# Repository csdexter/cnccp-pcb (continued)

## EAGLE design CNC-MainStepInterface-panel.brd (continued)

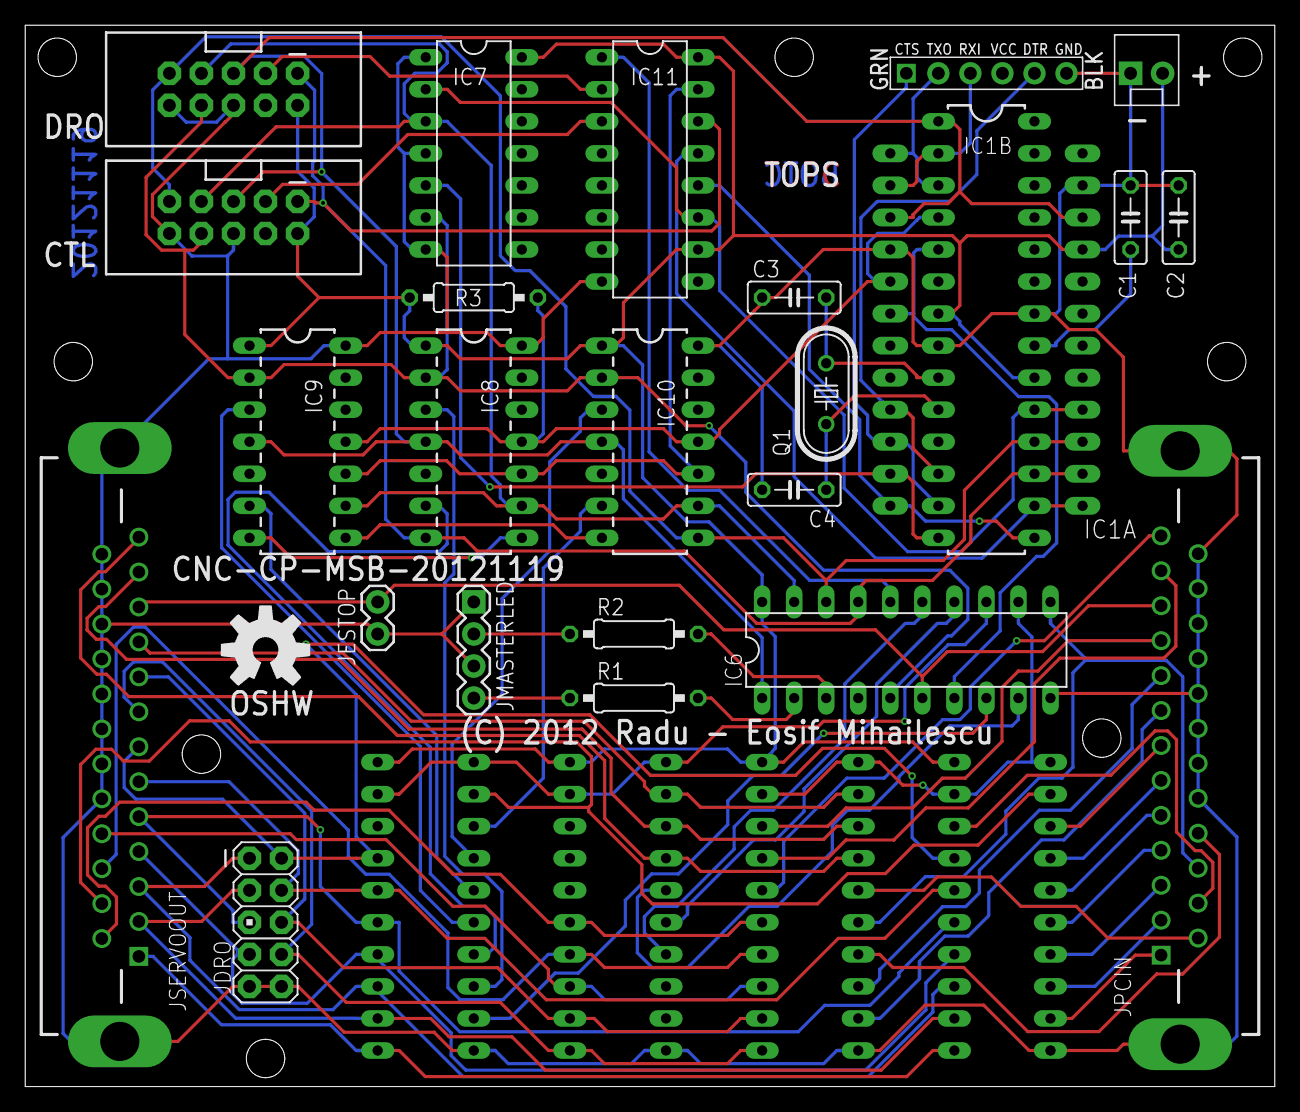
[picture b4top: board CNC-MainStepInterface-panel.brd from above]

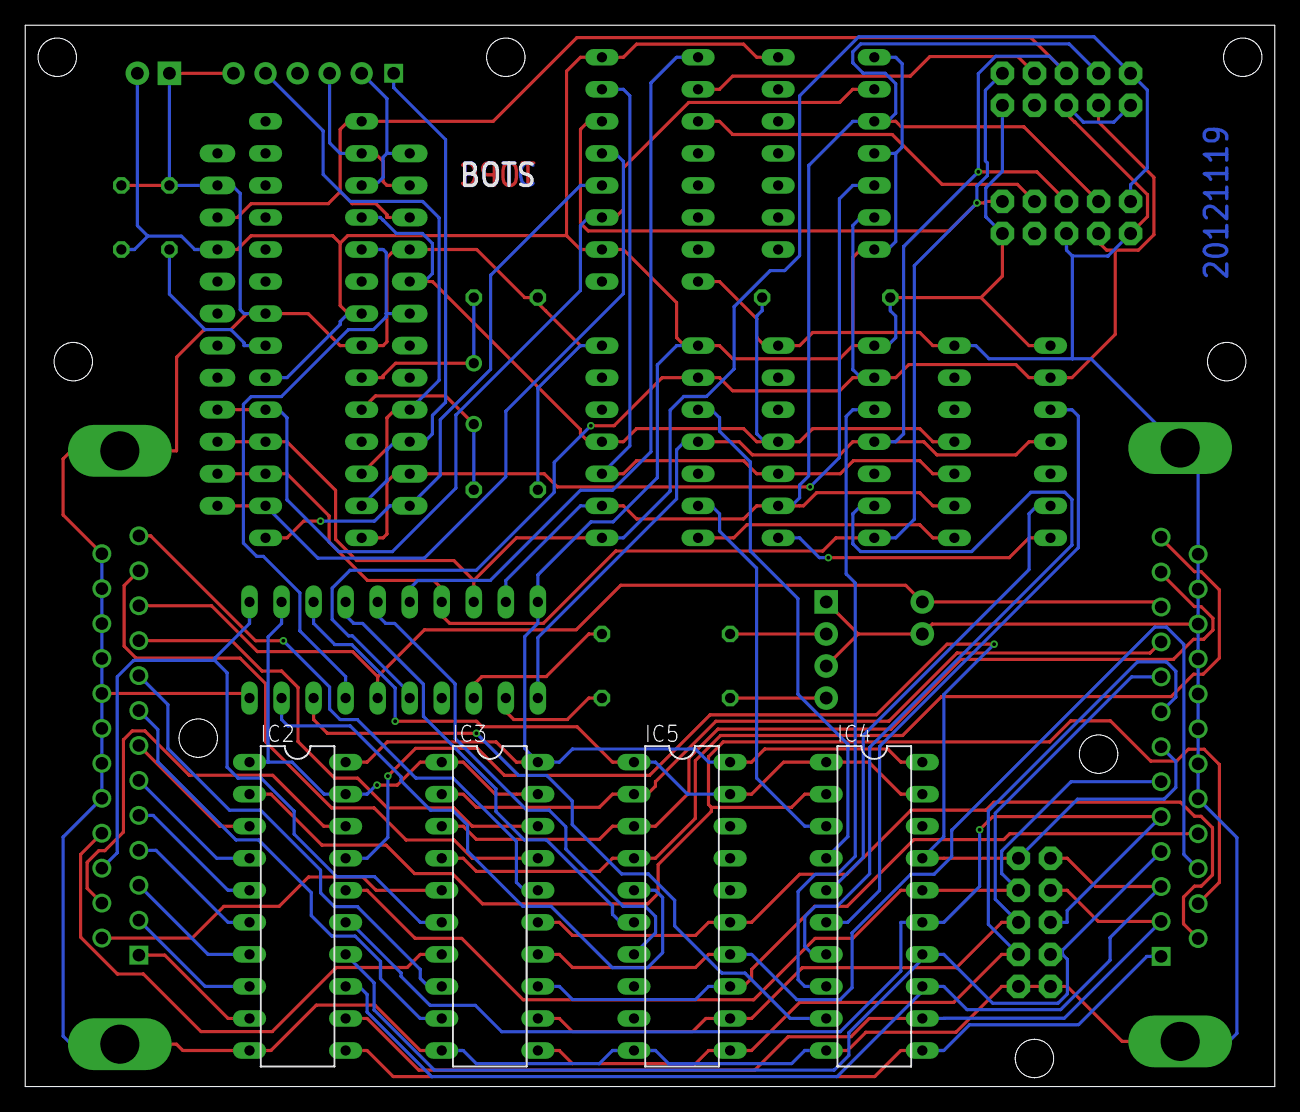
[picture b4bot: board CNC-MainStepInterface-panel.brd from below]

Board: 2 copper layers, 99.1 x 84.1 mm, 30 parts (4 on the bottom side), 78 nets.

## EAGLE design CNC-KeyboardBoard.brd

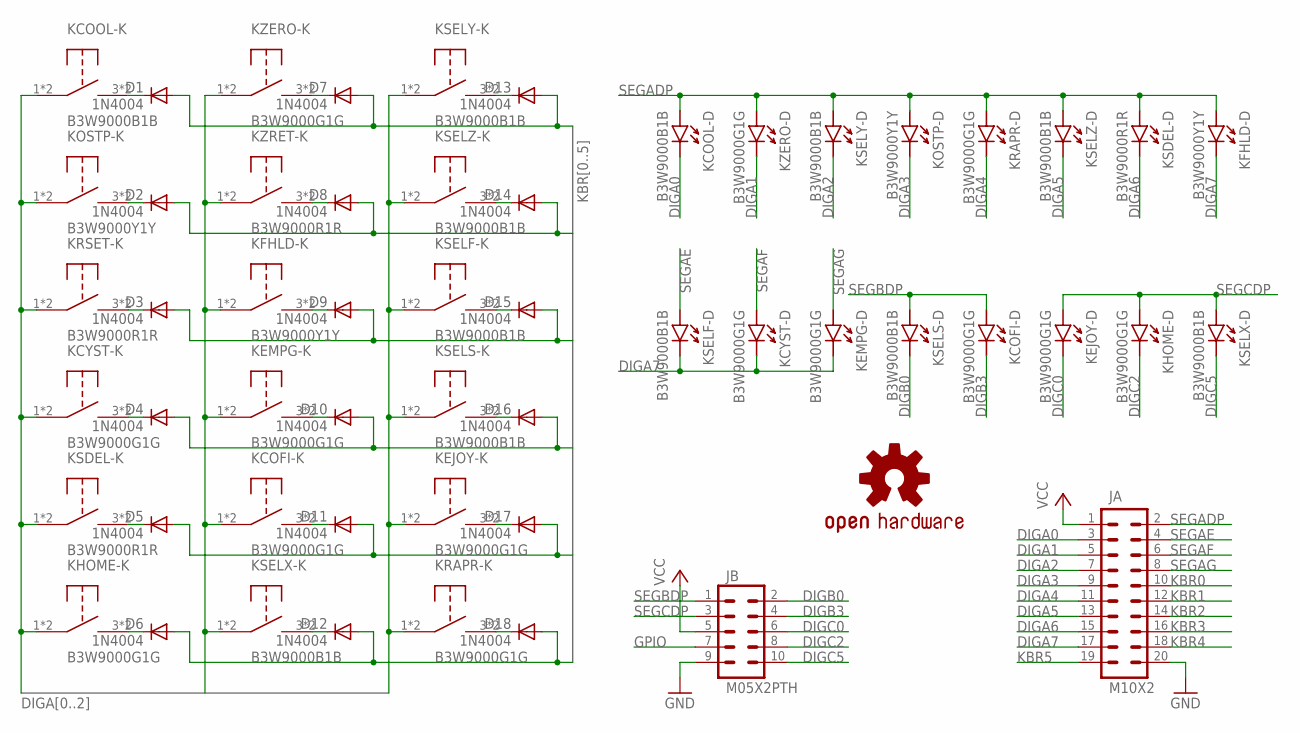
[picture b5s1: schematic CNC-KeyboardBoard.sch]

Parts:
D1, D2, D3, D4, D5, D6, D7, D8, D9, D10, D11, D12, D13, D14, D15, D16, D17, D18: 1N4004; DO41-10
JA: M10X2; 2X10
JB: M05X2PTH; AVR_ICSP
KCOFI: B3W9000G1G; OMRON_B3W90
KCOOL: B3W9000B1B; OMRON_B3W90
KCYST: B3W9000G1G; OMRON_B3W90
KEJOY: B3W9000G1G; OMRON_B3W90
KEMPG: B3W9000G1G; OMRON_B3W90
KFHLD: B3W9000Y1Y; OMRON_B3W90
KHOME: B3W9000G1G; OMRON_B3W90
KOSTP: B3W9000Y1Y; OMRON_B3W90
KRAPR: B3W9000G1G; OMRON_B3W90
KRSET: B3W9000R1R; OMRON_B3W90
KSDEL: B3W9000R1R; OMRON_B3W90
KSELF: B3W9000B1B; OMRON_B3W90
KSELS: B3W9000B1B; OMRON_B3W90
KSELX: B3W9000B1B; OMRON_B3W90
KSELY: B3W9000B1B; OMRON_B3W90
KSELZ: B3W9000B1B; OMRON_B3W90
KZERO: B3W9000G1G; OMRON_B3W90
KZRET: B3W9000R1R; OMRON_B3W90
U$1: SPARKFUN_OSHW-LOGOL; SPARKFUN_OSHW-LOGO-L

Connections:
DIGA0: JA.3, KCOOL.1, KCOOL.2, KCOOL.6 (K), KCYST.1, KCYST.2, KHOME.1, KHOME.2, KOSTP.1, KOSTP.2, KRSET.1, KRSET.2, KSDEL.1, KSDEL.2
DIGA1: JA.5, KCOFI.1, KCOFI.2, KEMPG.1, KEMPG.2, KFHLD.1, KFHLD.2, KSELX.1, KSELX.2, KZERO.1, KZERO.2, KZERO.6 (K), KZRET.1, KZRET.2
DIGA2: JA.7, KEJOY.1, KEJOY.2, KRAPR.1, KRAPR.2, KSELF.1, KSELF.2, KSELS.1, KSELS.2, KSELY.1, KSELY.2, KSELY.6 (K), KSELZ.1, KSELZ.2
DIGA3: JA.9, KOSTP.6 (K)
DIGA4: JA.11, KRAPR.6 (K)
DIGA5: JA.13, KSELZ.6 (K)
DIGA6: JA.15, KSDEL.6 (K)
DIGA7: JA.17, KCYST.6 (K), KEMPG.6 (K), KFHLD.6 (K), KSELF.6 (K)
DIGB0: JB.2, KSELS.6 (K)
DIGB3: JB.4, KCOFI.6 (K)
DIGC0: JB.6, KEJOY.6 (K)
DIGC2: JB.8, KHOME.6 (K)
DIGC5: JB.10, KSELX.6 (K)
GND: JA.20, JB.9
GPIO: JB.7
KBR0: D1.A, D7.A, D13.A, JA.10
KBR1: D2.A, D8.A, D14.A, JA.12
KBR2: D3.A, D9.A, D15.A, JA.14
KBR3: D4.A, D10.A, D16.A, JA.16
KBR4: D5.A, D11.A, D17.A, JA.18
KBR5: D6.A, D12.A, D18.A, JA.19
unnamed: D3.C, KRSET.3, KRSET.4
unnamed: D4.C, KCYST.3, KCYST.4
unnamed: D5.C, KSDEL.3, KSDEL.4
unnamed: D6.C, KHOME.3, KHOME.4
unnamed: D1.C, KCOOL.3, KCOOL.4
unnamed: D7.C, KZERO.3, KZERO.4
unnamed: D8.C, KZRET.3, KZRET.4
unnamed: D9.C, KFHLD.3, KFHLD.4
unnamed: D11.C, KCOFI.3, KCOFI.4
unnamed: D12.C, KSELX.3, KSELX.4
unnamed: D10.C, KEMPG.3, KEMPG.4
unnamed: D2.C, KOSTP.3, KOSTP.4
unnamed: D16.C, KSELS.3, KSELS.4
unnamed: D13.C, KSELY.3, KSELY.4
unnamed: D14.C, KSELZ.3, KSELZ.4
unnamed: D15.C, KSELF.3, KSELF.4
unnamed: D17.C, KEJOY.3, KEJOY.4
unnamed: D18.C, KRAPR.3, KRAPR.4
SEGADP: JA.2, KCOOL.5 (A), KFHLD.5 (A), KOSTP.5 (A), KRAPR.5 (A), KSDEL.5 (A), KSELY.5 (A), KSELZ.5 (A), KZERO.5 (A)
SEGAE: JA.4, KSELF.5 (A)
SEGAF: JA.6, KCYST.5 (A)
SEGAG: JA.8, KEMPG.5 (A)
SEGBDP: JB.1, KCOFI.5 (A), KSELS.5 (A)
SEGCDP: JB.3, KEJOY.5 (A), KHOME.5 (A), KSELX.5 (A)
VCC: JA.1, JB.5

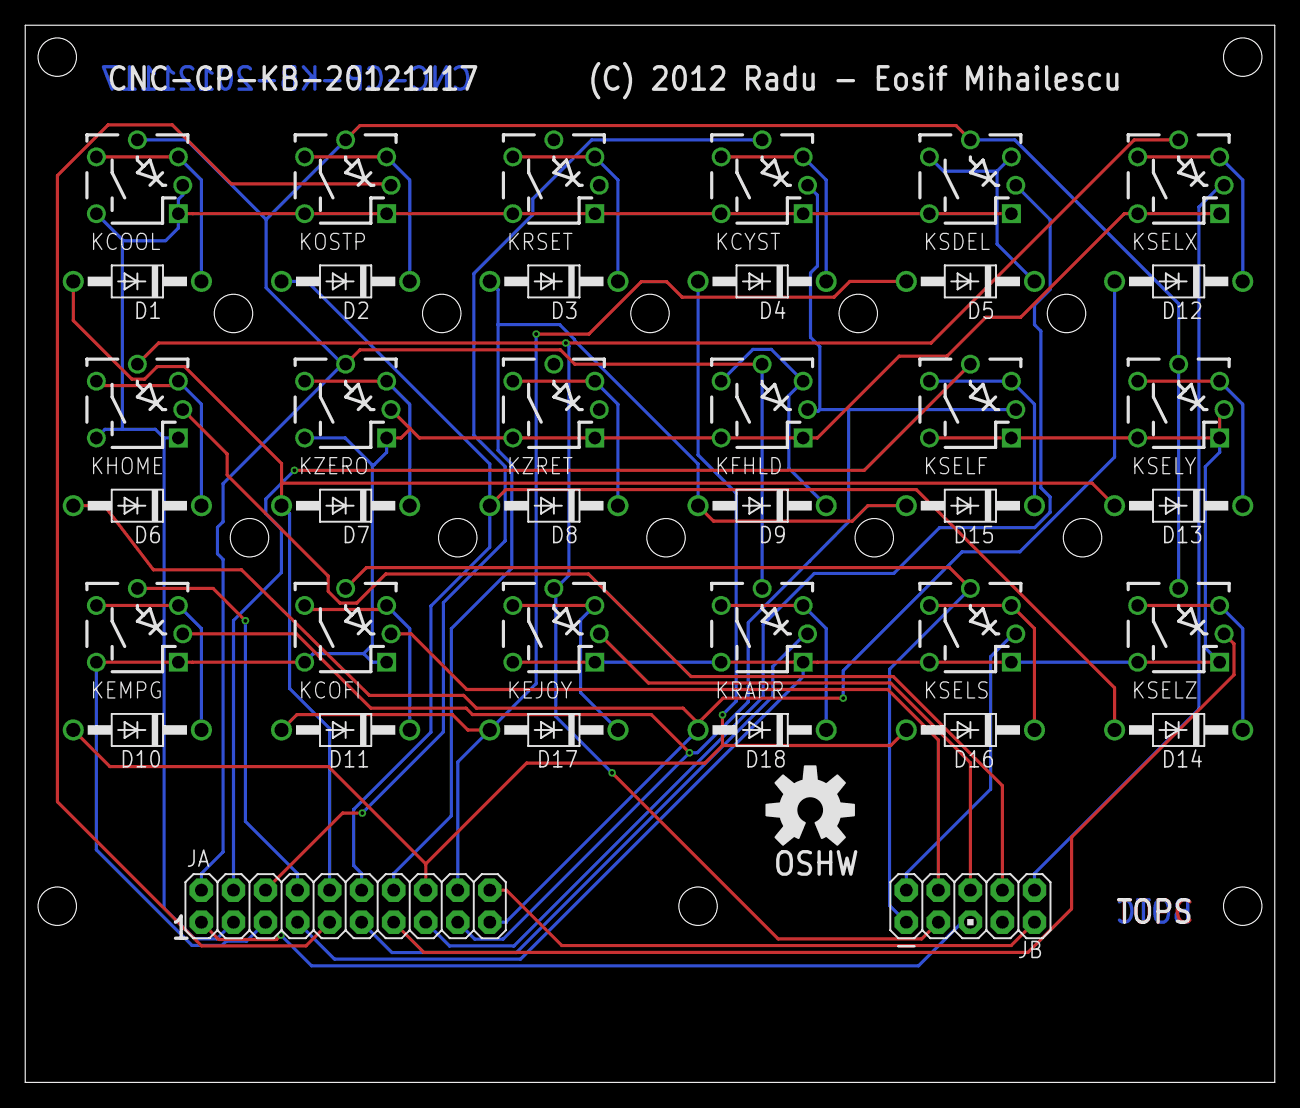
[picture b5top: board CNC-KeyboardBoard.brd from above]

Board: 2 copper layers, 99.1 x 83.8 mm, 39 parts (0 on the bottom side), 45 nets.

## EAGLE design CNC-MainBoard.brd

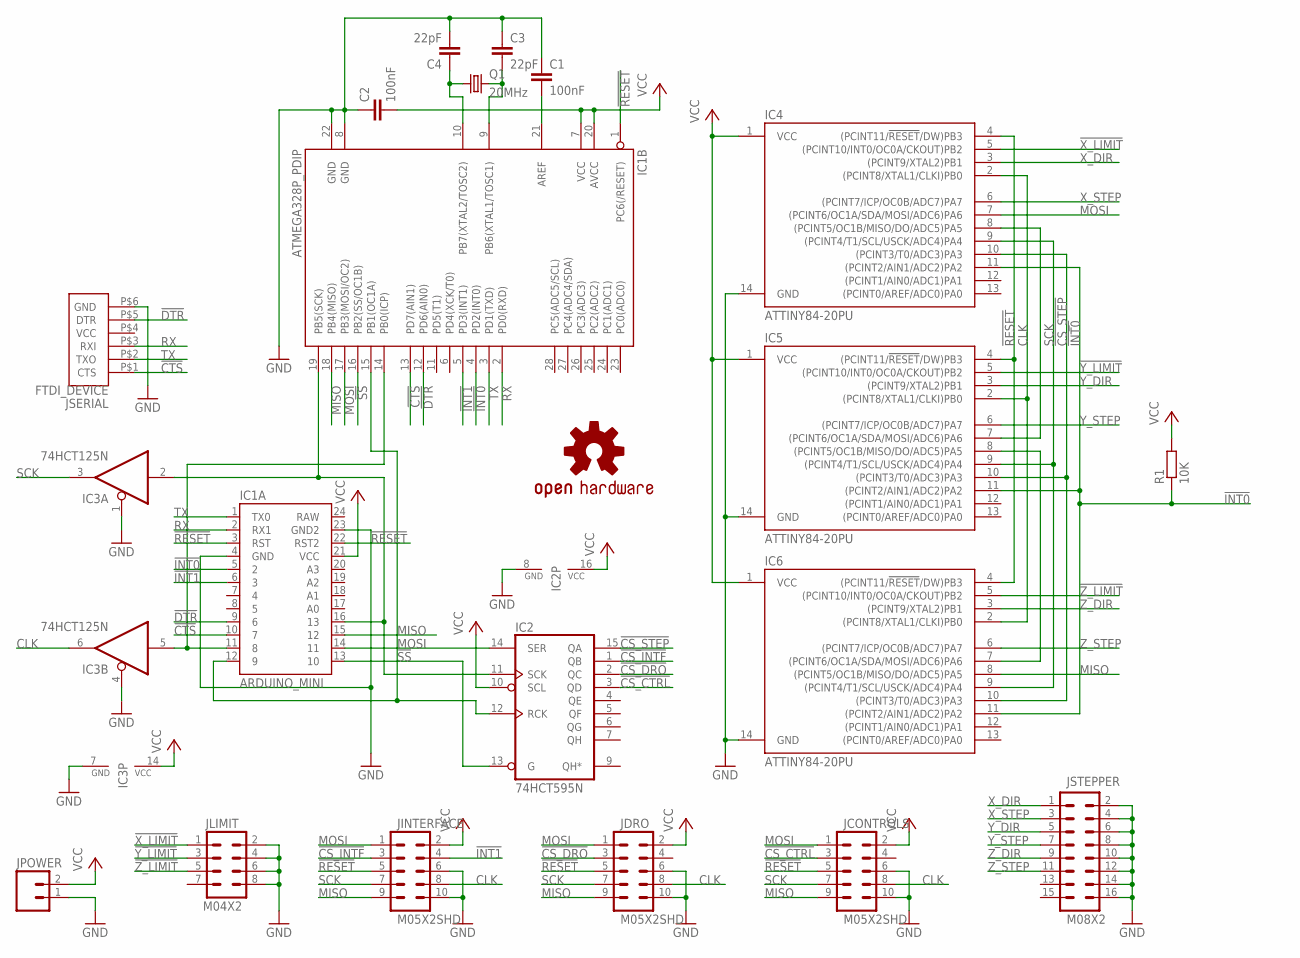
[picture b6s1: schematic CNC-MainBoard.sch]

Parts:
C1, C2: 100nF; C050-025X075
C3, C4: 22pF; C050-025X075
IC1A: ARDUINO_MINI
IC1B: ATMEGA328P_PDIP; DIL28-3
IC2: 74HCT595N; DIL16
IC3: 74HCT125N; DIL14
IC4, IC5, IC6: ATTINY84-20PU; DIL14
JCONTROLS: M05X2SHD; 2X5-SHROUDED
JDRO: M05X2SHD; 2X5-SHROUDED
JINTERFACE: M05X2SHD; 2X5-SHROUDED
JLIMIT: M04X2; 2X4
JPOWER: M02POLAR; MOLEX-1X2
JSERIAL: FTDI_DEVICE; FTDI_DEVICE_SIDE
JSTEPPER: M08X2; 2X8
Q1: 20MHz; HC49U-V
R1: 10K; 0207/10
U$1: SPARKFUN_OSHW-LOGOL; SPARKFUN_OSHW-LOGO-L

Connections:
!CS_CTRL: IC2.3 (QD), JCONTROLS.3
!CS_DRO: IC2.2 (QC), JDRO.3
!CS_INTF: IC2.1 (QB), JINTERFACE.3
!CS_STEP: IC2.15 (QA), IC4.10 ((PCINT3/T0/ADC3)PA3), IC5.10 ((PCINT3/T0/ADC3)PA3), IC6.10 ((PCINT3/T0/ADC3)PA3)
!CTS: IC1A.10 (7), IC1B.13 (PD7(AIN1)), JSERIAL.P$1 (CTS)
!DTR: IC1A.9 (6), IC1B.12 (PD6(AIN0)), JSERIAL.P$5 (DTR)
!INT0: IC1A.5 (2), IC1B.4 (PD2(INT0)), IC4.11 ((PCINT2/AIN1/ADC2)PA2), IC5.11 ((PCINT2/AIN1/ADC2)PA2), IC6.11 ((PCINT2/AIN1/ADC2)PA2), R1.1
!INT1: IC1A.6 (3), IC1B.5 (PD3(INT1)), JINTERFACE.4
!RESET: IC1A.3 (RST), IC1A.22 (RST2), IC1B.1 (PC6(/RESET)), IC4.4 ((PCINT11/!RESET!/DW)PB3), IC5.4 ((PCINT11/!RESET!/DW)PB3), IC6.4 ((PCINT11/!RESET!/DW)PB3), JCONTROLS.5, JDRO.5, JINTERFACE.5
!SS: IC1A.13 (10), IC1B.16 (PB2(SS/OC1B)), IC2.13 (G)
!X_LIMIT: IC4.5 ((PCINT10/INT0/OC0A/CKOUT)PB2), JLIMIT.1
!Y_LIMIT: IC5.5 ((PCINT10/INT0/OC0A/CKOUT)PB2), JLIMIT.3
!Z_LIMIT: IC6.5 ((PCINT10/INT0/OC0A/CKOUT)PB2), JLIMIT.5
CLK: IC3.6 (O), IC4.2 ((PCINT8/XTAL1/CLKI)PB0), IC5.2 ((PCINT8/XTAL1/CLKI)PB0), IC6.2 ((PCINT8/XTAL1/CLKI)PB0), JCONTROLS.8, JDRO.8, JINTERFACE.8
CLK_INT: IC1A.11 (8), IC1B.14 (PB0(ICP)), IC3.5 (I)
GND: C1.1, C2.1, C3.1, C4.2, IC1A.4 (GND), IC1A.23 (GND2), IC1B.8 (GND), IC1B.22 (GND), IC2.8 (GND), IC3.1 (OE), IC3.4 (OE), IC3.7 (GND), IC4.14 (GND), IC5.14 (GND), IC6.14 (GND), JCONTROLS.6, JCONTROLS.10, JDRO.6, JDRO.10, JINTERFACE.6, JINTERFACE.10, JLIMIT.2, JLIMIT.4, JLIMIT.6, JLIMIT.8, JPOWER.1, JSERIAL.P$6 (GND), JSTEPPER.2, JSTEPPER.4, JSTEPPER.6, JSTEPPER.8, JSTEPPER.10, JSTEPPER.12, JSTEPPER.14, JSTEPPER.16
MISO: IC1A.15 (12), IC1B.18 (PB4(MISO)), IC6.8 ((PCINT5/OC1B/MISO/DO/ADC5)PA5), JCONTROLS.9, JDRO.9, JINTERFACE.9
MISO_1: IC4.8 ((PCINT5/OC1B/MISO/DO/ADC5)PA5), IC5.7 ((PCINT6/OC1A/SDA/MOSI/ADC6)PA6)
MISO_2: IC5.8 ((PCINT5/OC1B/MISO/DO/ADC5)PA5), IC6.7 ((PCINT6/OC1A/SDA/MOSI/ADC6)PA6)
MOSI: IC1A.14 (11), IC1B.17 (PB3(MOSI/OC2)), IC2.14 (SER), IC4.7 ((PCINT6/OC1A/SDA/MOSI/ADC6)PA6), JCONTROLS.1, JDRO.1, JINTERFACE.1
unnamed: C1.2, IC1B.21 (AREF)
unnamed: C3.2, IC1B.9 (PB6(XTAL1/TOSC1)), Q1.2
unnamed: C4.1, IC1B.10 (PB7(XTAL2/TOSC2)), Q1.1
RX: IC1A.2 (RX1), IC1B.2 (PD0(RXD)), JSERIAL.P$3 (RXI)
SADDR: IC1A.12 (9), IC1B.15 (PB1(OC1A)), IC2.12 (RCK)
SCK: IC3.3 (O), IC4.9 ((PCINT4/T1/SCL/USCK/ADC4)PA4), IC5.9 ((PCINT4/T1/SCL/USCK/ADC4)PA4), IC6.9 ((PCINT4/T1/SCL/USCK/ADC4)PA4), JCONTROLS.7, JDRO.7, JINTERFACE.7
SCK_INT: IC1A.16 (13), IC1B.19 (PB5(SCK)), IC2.11 (SCK), IC3.2 (I)
TX: IC1A.1 (TX0), IC1B.3 (PD1(TXD)), JSERIAL.P$2 (TXO)
VCC: C2.2, IC1A.21 (VCC), IC1B.7 (VCC), IC1B.20 (AVCC), IC2.10 (SCL), IC2.16 (VCC), IC3.14 (VCC), IC4.1 (VCC), IC5.1 (VCC), IC6.1 (VCC), JCONTROLS.2, JDRO.2, JINTERFACE.2, JPOWER.2, R1.2
X_DIR: IC4.3 ((PCINT9/XTAL2)PB1), JSTEPPER.1
X_STEP: IC4.6 ((PCINT7/ICP/OC0B/ADC7)PA7), JSTEPPER.3
Y_DIR: IC5.3 ((PCINT9/XTAL2)PB1), JSTEPPER.5
Y_STEP: IC5.6 ((PCINT7/ICP/OC0B/ADC7)PA7), JSTEPPER.7
Z_DIR: IC6.3 ((PCINT9/XTAL2)PB1), JSTEPPER.9
Z_STEP: IC6.6 ((PCINT7/ICP/OC0B/ADC7)PA7), JSTEPPER.11

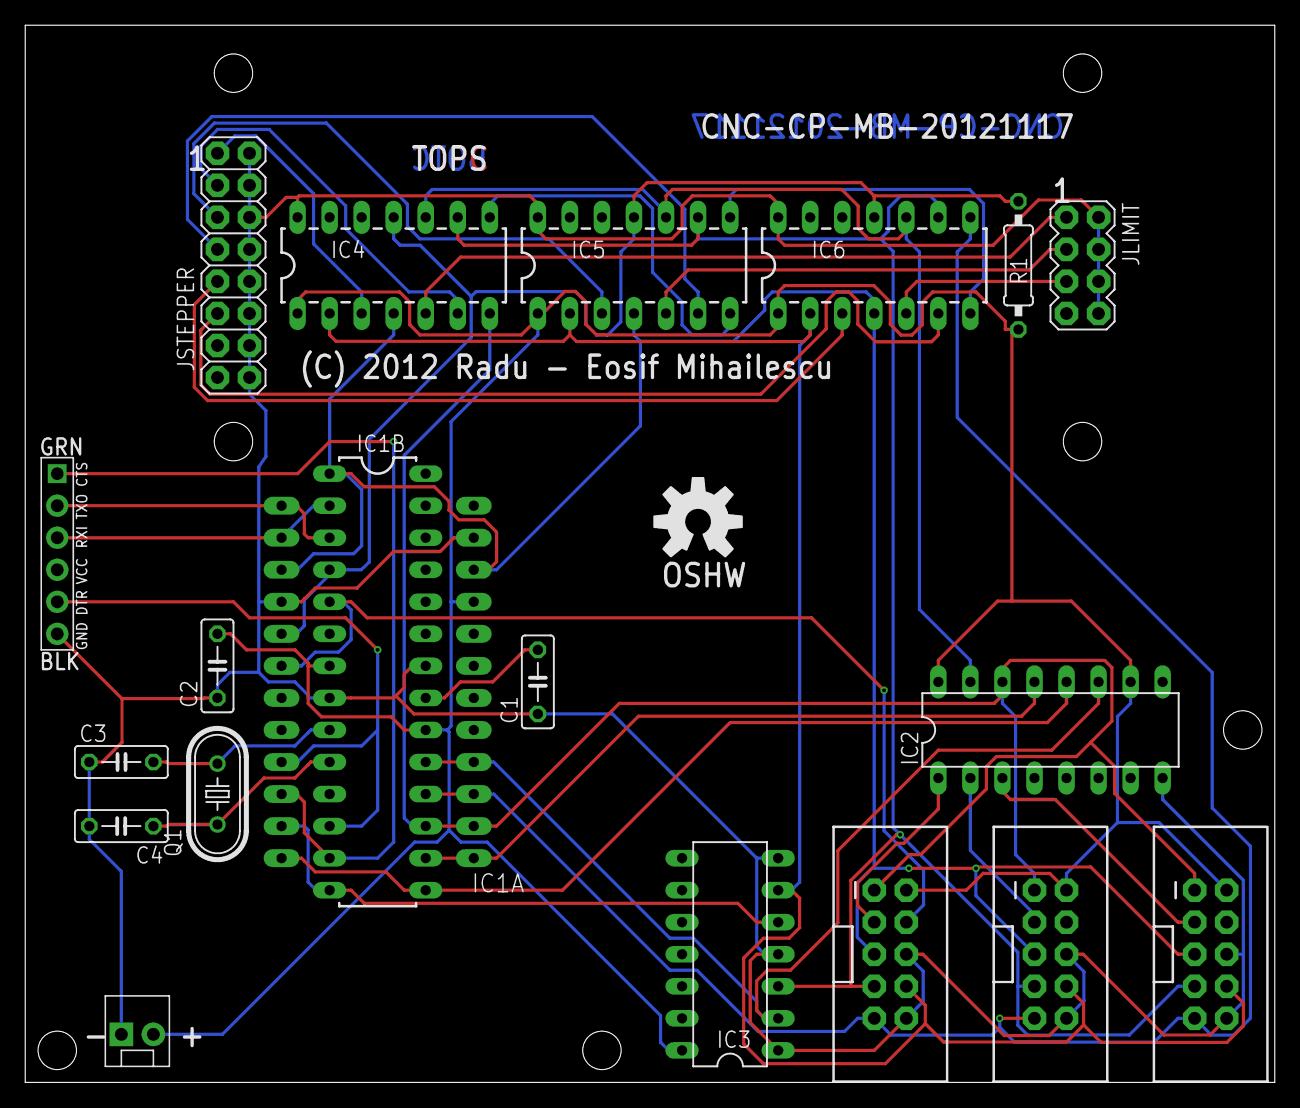
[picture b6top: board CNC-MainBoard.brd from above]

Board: 2 copper layers, 99.1 x 83.8 mm, 21 parts (0 on the bottom side), 35 nets.

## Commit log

2012-12-10 Initial commit: sync with local - initial version of all EDA files, corresponding to the 20121117/20121119 silkscreen version and to the 20121119 and 20121207 production runs - housekeeping: README, 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
2012-12-10 Minor cosmetic changes, following production run. - added 45 degree bends to all 90 corners - straightened up two traces
2012-12-10 BUGFIX: [XYZ]_LIMIT# not connected to [XYZ]_HOME# - when panelizing Main + Stepper + Interface on the same board, I forgot to make LIMIT the same as HOME. This will have to be reworked by hand during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
2012-12-12 BUGFIX: Assembly variants - variant "20MHz" did not exclude "Arduino Pro Mini", as it should have. Fixed.
2013-04-12 Update README.md
    - fixed typos and imporoved wording
2013-04-12 Housekeeping: - deleted obsolete Interface and Main -only boards and schematics. All these have been condensed in the MainStepInterface panel now - updated .gitignore to include library backups - upd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
2013-05-19 Added Synertex CL2 in all packaging versions.
2013-05-27 BUGFIX: 74LS4053 doesn't have the commons where you'd think it has - misleading symbol helped me mistake select inputs for common outputs - updated schematic, PCB update pending - this is probably no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
2013-05-28 BUGFIX: Same 4053 mistake fixed on Controls board as well UPDATE: 27k instead of 33k for Riset as all LEDs can handle 20mA at 2.1V - routed both DRO and Controls in FreeRouting - updated silkscreen/a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
2015-02-20 SNAPSHOT: - intermediate commit to checkpoint state
2015-02-21 UPDATE: - added various devices and footprints I used for the BreadBoard-PSU project.
2015-02-23 BUGFIX: - DC Power Jack was missing >NAME and >VALUE.
2015-04-02 Size adjustments after the first qualification run: - 50% pad restring for some footprints instead of the 25% default, aids manual assembly.
2016-05-01 ENHANCEMENT: added a couple Schurter power-entry -related parts.
2016-05-01 Revert "ENHANCEMENT: added a couple Schurter power-entry -related parts."
    This reverts commit 4fb299129f2cc539ea6eccf9612a81f69a061dab.
    Because, why not? When GitHub can ruin your day, why not?
2016-05-01 ENHANCEMENT: added a couple Schurter power-entry -related parts. - take 2, because why not? When stupid design meets stupid implementation and they both decide your day is better ruined? - one day so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
2016-08-14 UDPATE: Added MCP2562 and MCP2515 (CAN transceiver and controller).
2016-09-18 UPDATE: minor changes to footprints
2016-09-18 Added other bits and pieces from other, related, CNC projects.
2016-09-20 UPDATE: sized board outline to fit DIN rail mount frame and routed.
2016-09-21 RTM: aesthetics and shrink-wrap for the opto board, ready for tape-out.
2017-05-01 UPDATE: added LM319M - needed for AV123 subwoofer
2017-06-23 UPDATE: added ST LED2472G in TQFP48 - this will need to become TQFP48-EP - MLPQ40 version will also need to be added.
2017-12-15 UPDATE: added Peregrine PE42750 (symbol only for now)
2017-12-19 UPDATE: refined symbol and footprint for PE42742
2017-12-21 UPDATE: Added Maxim MAX9933 RF detector
2018-01-30 UPDATE: added TE IM43GR RF-compatible latching relay.
2018-02-02 UPDATE: added Microchip MTS62C19A, stepper driver.
2018-02-02 UPDATE: Added ON LV8549M, stepper driver.
